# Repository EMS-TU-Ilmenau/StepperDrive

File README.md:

# StepperDrive
This embedded project features a simple controller board for a stepper motor. 
Multiple boards can be connected together. 
One of it has to be attached to USB and power supply. 
Each motor can then be controlled with simple SCPI-like commands via UART (8N1 9600baud) to move to a position, set the maximum rate and acceleration etc.

## Features
- Uses TMC2209 stepper driver IC for smooth and quiet operation
- Multiple boards can be connected to each other via ethernet-cables
- USB-C interface for control and flashing firmware

Note that there is no real anti-collision protocol, but as the communication is quit fast, there should be no problem to query each motors parameters individually with their IDs after another.
E.g. `AX1:POS?` then `AX2:POS?`.
Sending commands can be even done simultaneously, e.g. `AX1:POS 180;AX2:POS 22.5`.

## Flashing
The firmware is written in AVR-C for the ATtiny814. To start programming, an extended AVR toolchain is needed, which can be found in the Arduino IDE (the GNU AVR toolchain does NOT support the ATtiny814):
- Go to https://www.arduino.cc/en/software and scroll down to "legacy IDE (1.8.X)" and download the zipped version for your OS
- Unzip and add 
  - (Linux) *arduino-1.8.19-linux64.tar/arduino-1.8.19-linux64/arduino-1.8.19/hardware/tools/avr/bin* or 
  - (Windows) *arduino-1.8.19-windows\arduino-1.8.19\hardware\tools\avr\bin* 
  
  to your systems PATH variable (the rest of the IDE is not needed)
- Install [Make](https://www.gnu.org/software/make/#download) if you have it not already

To transfer the firmware to the microcontroller, install [pymcuprog](https://pypi.org/project/pymcuprog/).
Switch to **Prog** on the PCB.
Edit the PROGRAMMER variable (serial port) in the [firmware/Makefile](Makefile) and run `make flash clean` to build, flash and remove the built files.

## Commands
#### Common rules
Commands are simple ascii strings (no binary shenanigans, so human readable), terminated with `\n` (linefeed).
The string length must not exceed 64 chars in total (could be raised probably, not tested).
The commands have to be send with 9600 baud, 8 byte, no parity and 1 stop bit (8N1).

At the moment, only one command is parsed for each axis at a time, i.e. it is not possible to set the rate and position for a motor in one string.
However, it is possible to send one command to each motor simultaneously, by separating the commands with semicolons.
You can send commands and receive replies while the motor is moving, e.g. you can set a new position - the motor will instantly move to that position even it has not reached its last target position.

All commands must begin with `AX`, followed by the axis identifier number (default `1`) as specified with `AX1:ID <1...9>` (saved in EEPROM). 
If you forgot the ID, you can query it (works only when one controller board is connected to the hub) using `*IDN?`.

All parameters and subparameters have to be separated with a colon (`:`), followed by either a query (`?`) or the value.
E.g. `AX1:POS?`, `AX4:POW ON`, `AX2:LIM:MAX 360` or `AX3:SUB2`.
Note that the questionmark must follow immediately, while a value can have a leading white space (not required though).
When setting a parameter, it is possible to add `;*OPC?` afterwards to get feedback (`1` is returned) when the operation completed.

Commands are case-sensitive (all capital letters).

#### List of commands
- `:POW` [`ON` or `OFF`] Motor power on or off. Probably the first thing you do is to turn the power on. Default `OFF`.
- `:ACC` [positive integer] Acceleration factor. This controls how smooth the movement to a target position starts. A value of `1` is very smooth, while `100` is like constante rate. Default is `100`.
- `:DEC` [positive integer] Decceleration factor. This controls how smooth the movement to a target position ends. A value of `1` is very smooth, while `100` is like constante rate. Default is `10`.
- `:HOME` [float or integer] Moves the motor with given velocity in degree/s until the home sense pin goes low. After that, the position is defined as 0 degree. When requested, the reply is either `1` (at home) or `0` not homed/homing in progress.
- `:POS` [float or integer] Axis position (angle) in degree.
- `:LIM:MAX` [positive float or integer] Upper speed limit in degree/s. Must not be set higher than `8000*360/(substeps*steps_per_revolution)` (steps per revolution is set the in makefile and is 200 for most motors). Default 360.
- `:LIM:MIN` [positive float or integer] Lower speed limit in degree/s. Must not be set to 0. Default 10.
- `:RATE` [positive float or integer] Shorthand for `:LIM:MAX`.
- `:VEL` [positive float or integer] Rotates the axis infinitely with value in degree/s.
- `:SUB` [`8`, `16`, `32` or `64`] Number of substeps. Higher values will result in finer resolution and smoother movements, but also lower maximum rate. Default is `8`. **Important:** Set the substeps before setting or getting any parameter with degree related unit.

## TODOs
Currently, the TMC2209 is controlled via classic STEP, DIR, ENABLE, MS pins by the firmware. The hardware supports to configure the driver via its UART interface, for example to enable stall detection.

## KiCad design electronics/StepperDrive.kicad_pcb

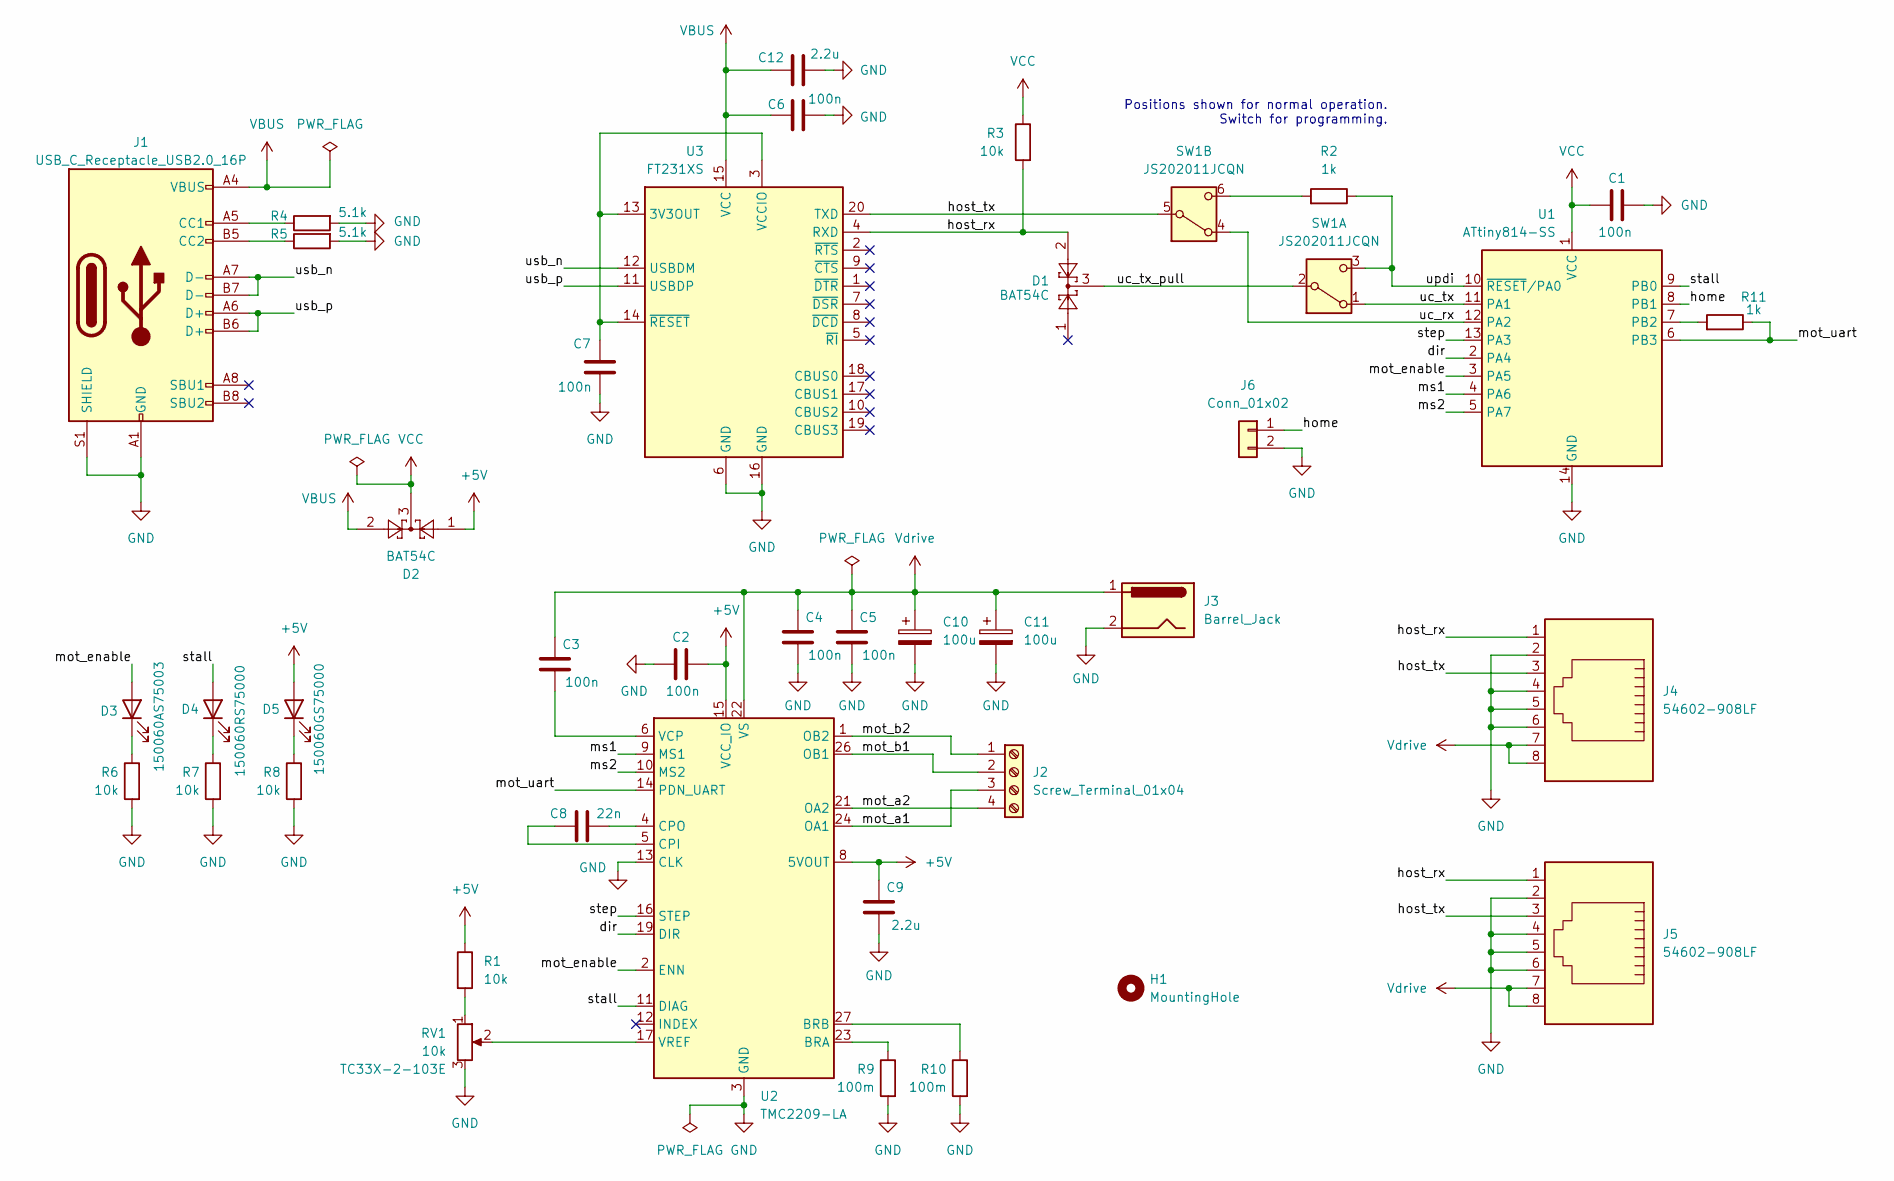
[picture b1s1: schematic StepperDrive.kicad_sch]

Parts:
C1, C2, C3, C4, C5, C6, C7: 100n; C_0603_1608Metric_Pad1.08x0.95mm_HandSolder
C8: 22n; C_0603_1608Metric_Pad1.08x0.95mm_HandSolder
C9, C12: 2.2u; C_0603_1608Metric_Pad1.08x0.95mm_HandSolder
C10, C11: 100u; CP_Elec_6.3x9.9
D1, D2: BAT54C; SOT-23
D3: 150060AS75003; LED_0603_1608Metric_Pad1.05x0.95mm_HandSolder
D4: 150060RS75000; LED_0603_1608Metric_Pad1.05x0.95mm_HandSolder
D5: 150060GS75000; LED_0603_1608Metric_Pad1.05x0.95mm_HandSolder
H1: MountingHole; MountingHole_3.2mm_M3_DIN965
J1: USB_C_Receptacle_USB2.0_16P; USB_C_Receptacle_GCT_USB4105-xx-A_16P_TopMnt_Horizontal
J2: Screw_Terminal_01x04; TerminalBlock_bornier-4_P5.08mm
J3: Barrel_Jack; BarrelJack_CUI_PJ-079BH_Horizontal
J4, J5: 54602-908LF; RJ45_Amphenol_54602-x08_Horizontal
J6: Conn_01x02; PinHeader_1x02_P2.54mm_Vertical
R1, R3, R6, R7, R8: 10k; R_0603_1608Metric_Pad0.98x0.95mm_HandSolder
R2, R11: 1k; R_0603_1608Metric_Pad0.98x0.95mm_HandSolder
R4, R5: 5.1k; R_0603_1608Metric_Pad0.98x0.95mm_HandSolder
R9, R10: 100m; R_0805_2012Metric_Pad1.20x1.40mm_HandSolder
RV1: 10k; Potentiometer_Bourns_TC33X_Vertical; MPN TC33X-2-103E
SW1: JS202011JCQN; SW_DPDT_CK_JS202011JCQN
U1: ATtiny814-SS; SOIC-14_3.9x8.7mm_P1.27mm
U2: TMC2209-LA; QFN-28-1EP_5x5mm_P0.5mm_EP3.75x3.75mm
U3: FT231XS; SSOP-20_3.9x8.7mm_P0.635mm

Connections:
+5V: C2.2, C9.2, D2.1, D5.2 (A), R1.1, U2.8 (5VOUT), U2.15 (VCC_IO)
/dir: U1.2 (PA4), U2.19 (DIR)
/home: J6.1, U1.8 (PB1)
/host_rx: D1.2, J4.1, J5.1, R3.2, U3.4 (RXD)
/host_tx: J4.3, J5.3, SW1.5 (B), U3.20 (TXD)
/mot_a1: J2.3, U2.24 (OA1)
/mot_a2: J2.4, U2.21 (OA2)
/mot_b1: J2.2, U2.26 (OB1)
/mot_b2: J2.1, U2.1 (OB2)
/mot_enable: D3.2 (A), U1.3 (PA5), U2.2 (ENN)
/mot_uart: R11.1, U1.6 (PB3), U2.14 (PDN_UART)
/ms1: U1.4 (PA6), U2.9 (MS1)
/ms2: U1.5 (PA7), U2.10 (MS2)
/stall: D4.2 (A), U1.9 (PB0), U2.11 (DIAG)
/step: U1.13 (PA3), U2.16 (STEP)
/uc_rx: SW1.4 (A), U1.12 (PA2)
/uc_tx: SW1.1 (A), U1.11 (PA1)
/uc_tx_pull: D1.3, SW1.2 (B)
/updi: R2.1, SW1.3 (C), U1.10 (~RESET/PA0)
/usb_n: J1.A7 (D-), J1.B7 (D-), U3.12 (USBDM)
/usb_p: J1.A6 (D+), J1.B6 (D+), U3.11 (USBDP)
GND: C1.1, C2.1, C4.1, C5.1, C6.1, C7.1, C9.1, C10.2, C11.2, C12.1, J1.A1 (GND), J1.A12 (GND), J1.B1 (GND), J1.B12 (GND), J1.S1 (SHIELD), J3.2, J4.2, J4.4, J4.5, J4.6, J5.2, J5.4, J5.5, J5.6, J6.2, R4.2, R5.2, R6.2, R7.2, R8.2, R9.2, R10.2, RV1.3, U1.14 (GND), U2.3 (GND), U2.13 (CLK), U2.18 (GND), U2.29 (EP), U3.6 (GND), U3.16 (GND)
unnamed: D3.1 (K), R6.1
unnamed: D4.1 (K), R7.1
unnamed: D5.1 (K), R8.1
unnamed: J1.A5 (CC1), R4.1
unnamed: J1.B5 (CC2), R5.1
unnamed: R1.2, RV1.1
unnamed: R2.2, SW1.6 (C)
unnamed: R11.2, U1.7 (PB2)
unnamed: R9.1, U2.23 (BRA)
unnamed: R10.1, U2.27 (BRB)
unnamed: C8.2, U2.5 (CPI)
unnamed: C8.1, U2.4 (CPO)
unnamed: C3.1, U2.6 (VCP)
unnamed: RV1.2, U2.17 (VREF)
unnamed: C7.2, U3.3 (VCCIO), U3.13 (3V3OUT), U3.14 (~RESET)
VBUS: C6.2, C12.2, D2.2, J1.A4 (VBUS), J1.A9 (VBUS), J1.B4 (VBUS), J1.B9 (VBUS), U3.15 (VCC)
VCC: C1.2, D2.3, R3.1, U1.1 (VCC)
Vdrive: C3.2, C4.2, C5.2, C10.1, C11.1, J3.1, J4.7, J4.8, J5.7, J5.8, U2.22 (VS), U2.28 (VS)

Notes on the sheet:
Positions shown for normal operation. Switch for programming.

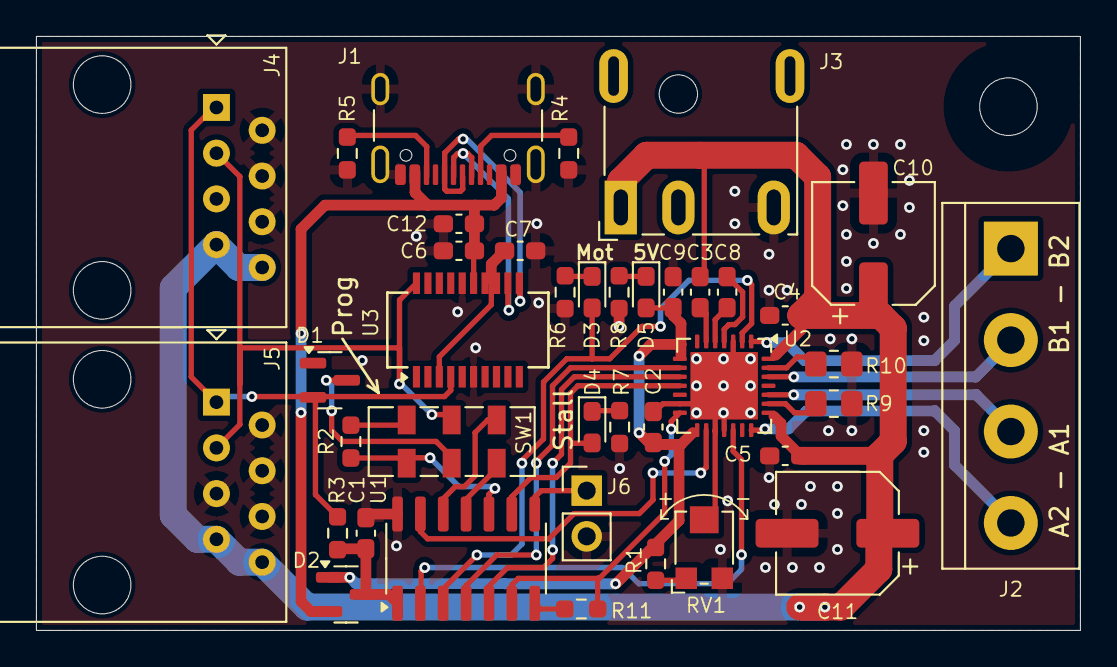
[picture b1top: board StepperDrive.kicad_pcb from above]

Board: 2 copper layers, 58.0 x 33.0 mm, 40 parts (0 on the bottom side), 40 nets.

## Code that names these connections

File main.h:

#include <avr/io.h> // for pin definitions
#include <stdint.h> // for data types

// define macros and constants
#define STR_HELPER(x) #x
#define STR(x) STR_HELPER(x)
#define TRUE 1
#define FALSE 0
#define HOME_OFF 0 // homing states
#define HOME_SEARCH 1
#define HOME_FOUND 2
#define HOME_ON 3
#define UART_BAUD 9600UL
#define UART_UBRR (F_CPU/(8*UART_BAUD)-1) // calculate register value for baudrate for U2Xn = 1
#define UART_MAXSTRLEN 64
#define STR_TERM '\n'
#define RADIX 10 // for itoa
#define F_TINT 8000 // timer interrupt frequency
#define C_PRESC 64 // control frequency that much slower than F_TINT
#define CMD_ID "AX" STR(AX_ID) // axis specific commands must start with AX<id>
#define PIN_ENABLE PA6 // motor enable pin (low active)
#define PIN_STEP PB1 // motor step pin
#define PIN_DIR PB0 // motor direction pin
#define PIN_LED PA0 // status or testing LED pin
#define PIN_HOME PA4 // homing switch pin (low active)
#define PIN_SS1 PA7 // substep bit 1
#define PIN_SS2 PB2 // substep bit 2
#define PIN_SS3 PA3 // substep bit 3

// structs
typedef struct {
	// for a P control loop
	int32_t tarStepPos;
	int32_t curStepPos;
	int32_t oldStepPos;
	uint16_t tic;
	uint16_t stepPeriod;
	int8_t tarDir;
} pCtrl_t;

// variables
char uartReceiveStr[UART_MAXSTRLEN] = "";
char uartSendStr[UART_MAXSTRLEN] = "";
uint8_t gotCommand = FALSE;
volatile uint8_t gotControlReq = FALSE;
uint8_t substeps = 4; // num of microsteps which make 1 full step
uint16_t maxStepRate, minStepRate; // step rate limits
uint16_t kAcc = 100; // acceleration proportion
uint16_t kDec= 10; // decceleration proportion
uint8_t homing = HOME_OFF; // homing state
pCtrl_t ctrlState;

// prototypes
void GPIO_Init();
void USART0_Init();
void USART0_ReceiveChar();
void USART0_SendChar(const char c);
void USART0_SendString(const char* strP);
void ParseCommand(const char* strP);
void Timer0_Init();
int32_t DegToSteps(int32_t deg);
int32_t StepsToDeg(int32_t steps);
void SendNum(int16_t num);
void Control(pCtrl_t* ctrlP);
void PhyStep(pCtrl_t* ctrlP);
void SetSubsteps(uint8_t ss);
int32_t DegStrToSteps(const char* strP);
void SendStepsAsDeg(int32_t steps);

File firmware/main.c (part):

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		}

		// check for home
		if ((homing == search) && (!(PORTB.IN & PIN_HOME))) {
			// switch activated, stop motor
			ctrlState.curStepPos = 0;
			ctrlState.tarStepPos = 0;
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
void configGPIO() {
	// inputs
	PORTB.DIRCLR = PIN_STALL | PIN_HOME;
	PORTB.PIN1CTRL |= PORT_PULLUPEN_bm; // enable pullup for home

	// outputs
	PORTA.DIRSET = PIN_ENABLE | PIN_STEP | PIN_DIR | PIN_MS1 | PIN_MS2;
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	USART0.CTRLA |= USART_RXCIF_bm; // enable interrupt on receive complete
	// use alternative UART pins
	PORTMUX_CTRLB |= PORTMUX_USART0_bm; // enable alternative UART pins
	PORTA.DIRCLR = PIN2_bm; // PA2 as input (RX)
	PORTA.DIRSET = PIN1_bm; // PA1 as output (TX)
}

void sendUARTChar(const char c) {
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
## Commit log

2017-10-18 Added notes why the ugly PCB
2017-10-18 Inverted PCB images to make it more printer friendly
2017-10-18 Try to make schematic and PCB images appear next to each other
2017-12-05 Fixed bug that caused to ignore the first received message from the host. Requesting the IDN now only returns the actual axis identifier.
2017-12-05 The first message from the host is still ignored because of hardware reasons (serial port produces random bytes when plugged), so reverted the fix
2019-09-02 Added rate parameter as shorthand for LIM:MAX for compatibility to old pcb
2019-09-03 Removed author. Added more infos about flashing
2020-05-28 Fixed setting 16 substeps
2020-05-29 added acceleration. Replaced KP by ACC and DEC factors
2020-07-01 replaced sendNum by correct parsing functions for each parameter
2020-07-01 to reduce interrupts, USART chars are now received in main loop. String termination is now only linefeed
2020-07-01 updated documentation about the string termination change to linefeed only
2024-05-16 added *OPC? command
2024-05-16 all new board with TMC2209 driver and without the need of an hub.
2024-05-17 fixed potential problem when reading or writing the axis ID
2024-05-17 added GND Via for stall LED
2024-05-17 minor fixes for potential problems
2024-05-22 removed repeated eeprom read as there seems no effect. Fixed float parsing
2024-05-22 fixed float parsing
